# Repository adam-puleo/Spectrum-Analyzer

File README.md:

# Spectrum-Analyzer
Uses the MSGEQ7 chips and a NeoPixel matrix to display frequency volumes using a Particle Photon.

This project uses two MSGEQ7 chips (COM-10468 on SparkFun.com) to analyze sound frequencies. One chip for the left, and the other chip for the right channel. Input is via a 3.5mm audio jack. The frequency volumes, and average volume is displayed with a NeoPixel matrix (COM-13304 on SparkFun.com). Data is processed using Particle's Photon (particle.io).

The Photon uses 3.3 volts on its analog and digital pins. The MSGEQ7 and NeoPixels are 5 volts. A SN74HCT125N is used to drive the inputs on the MSGEQ7 and NeoPixel from the Photon. To read the MSGEQ7s output a voltage divider circuit is used. The MSGEQ7 seems to output 4.8 volts when a frequency is at maximum volume thus a 1.5k ohm resistor is used. Pin eight of the SN74HCT125N is used to drive the NeoPixel matrix. Gate B, output pin 6, of the SN74HCT125N is not used.

The msgeq7, spectrum_display, and neopixelmatrix libraries have been published to Particle's public libraries. Thus when you compile the code Particle will automatically link with the libraries. The 'Eagle/Audio Lights' directory contains the schematic in Autodesk's EAGLE program.

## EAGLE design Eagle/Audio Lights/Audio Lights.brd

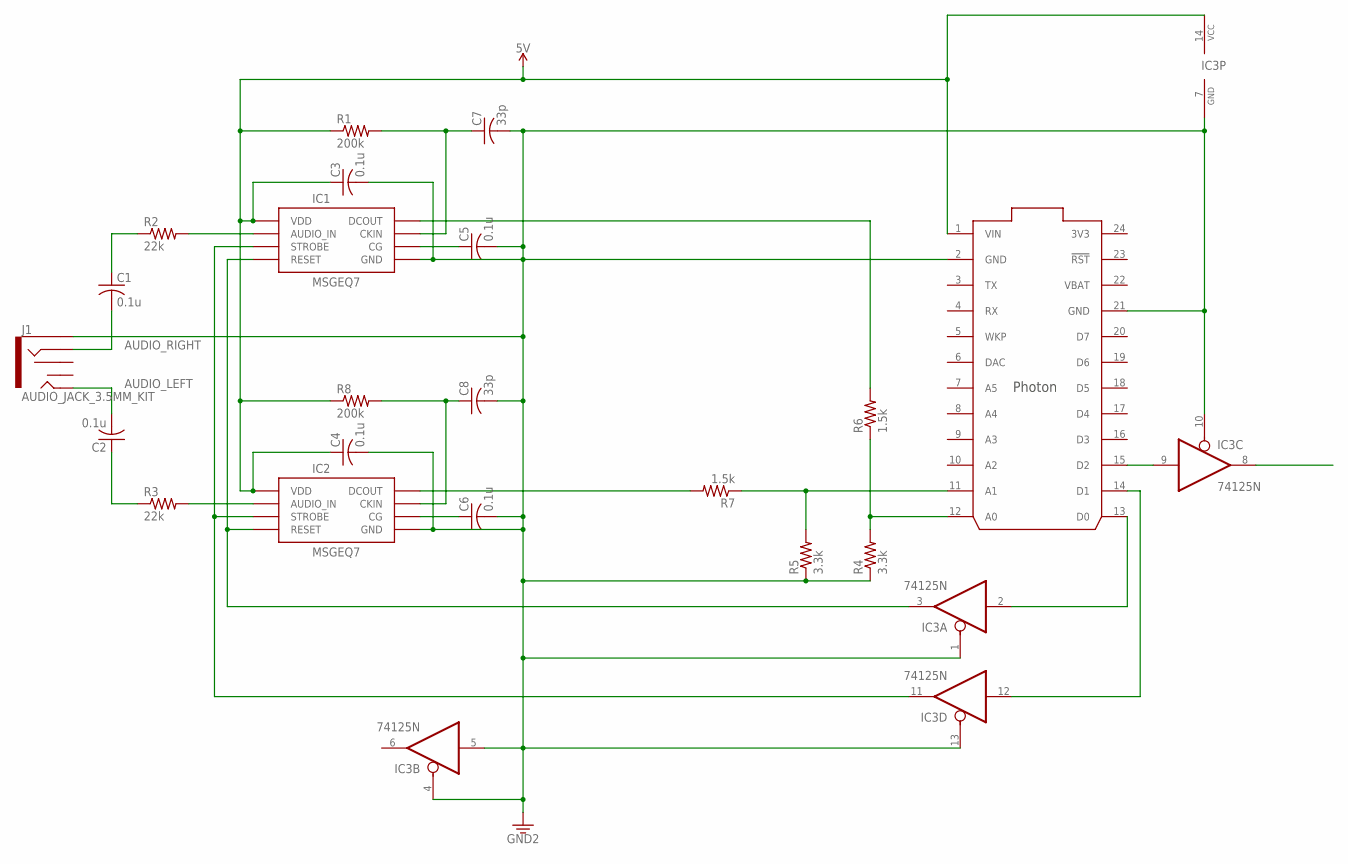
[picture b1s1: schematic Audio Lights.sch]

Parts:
C1, C2, C3, C4, C5, C6: 0.1u; C025-024X044
C7, C8: 33p; C050-045X075
IC1, IC2: MSGEQ7P; DIP08
IC3: 74125N; DIL14
J1: AUDIO_JACK_3.5MM_KIT; AUDIO-JACK-KIT
R1, R8: 200k; 0204/7
R2, R3: 22k; 0204/7
R4, R5: 3.3k; 0204/5
R6, R7: 1.5k; 0204/5
U$1: PHOTON_WITH_HEADERS; PHOTON

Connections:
3V3: U$1.24 (3V3)
5V: C3.1, C4.1, IC1.1 (VDD), IC2.1 (VDD), IC3.14 (VCC), R1.1, R8.1, U$1.1 (VIN)
AGND_LEFT: C6.1, IC2.6 (CG)
AGND_RIGHT: C5.1, IC1.6 (CG)
AUDIO_IN_LEFT: IC2.5 (AUDIO_IN), R3.2
AUDIO_IN_RIGHT: IC1.5 (AUDIO_IN), R2.2
AUDIO_LEFT: C2.2, J1.TIP
AUDIO_RIGHT: C1.2, J1.RING
CLK_LEFT: C8.1, IC2.8 (CKIN), R8.2
CLK_RIGHT: C7.1, IC1.8 (CKIN), R1.2
DOUT_LEFT3V3: R5.2, R7.1, U$1.11 (A1)
DOUT_LEFT5V: IC2.3 (DCOUT), R7.2
DOUT_RIGHT3V3: R4.2, R6.1, U$1.12 (A0)
DOUT_RIGHT5V: IC1.3 (DCOUT), R6.2
GND: C3.2, C4.2, C5.2, C6.2, C7.2, C8.2, IC1.2 (GND), IC2.2 (GND), IC3.1 (OE), IC3.4 (OE), IC3.5 (I), IC3.7 (GND), IC3.10 (OE), IC3.13 (OE), J1.SLEEVE, R4.1, R5.1, U$1.2 (GND), U$1.21 (GND)
LED_3.3V: IC3.9 (I), U$1.15 (D2)
LED_5V: IC3.8 (O)
unnamed: C2.1, R3.1
unnamed: C1.1, R2.1
RESET_3.3V: IC3.2 (I), U$1.13 (D0)
RESET_5V: IC1.7 (RESET), IC2.7 (RESET), IC3.3 (O)
STROBE_3.3V: IC3.12 (I), U$1.14 (D1)
STROBE_5V: IC1.4 (STROBE), IC2.4 (STROBE), IC3.11 (O)
VBAT: U$1.22 (VBAT)

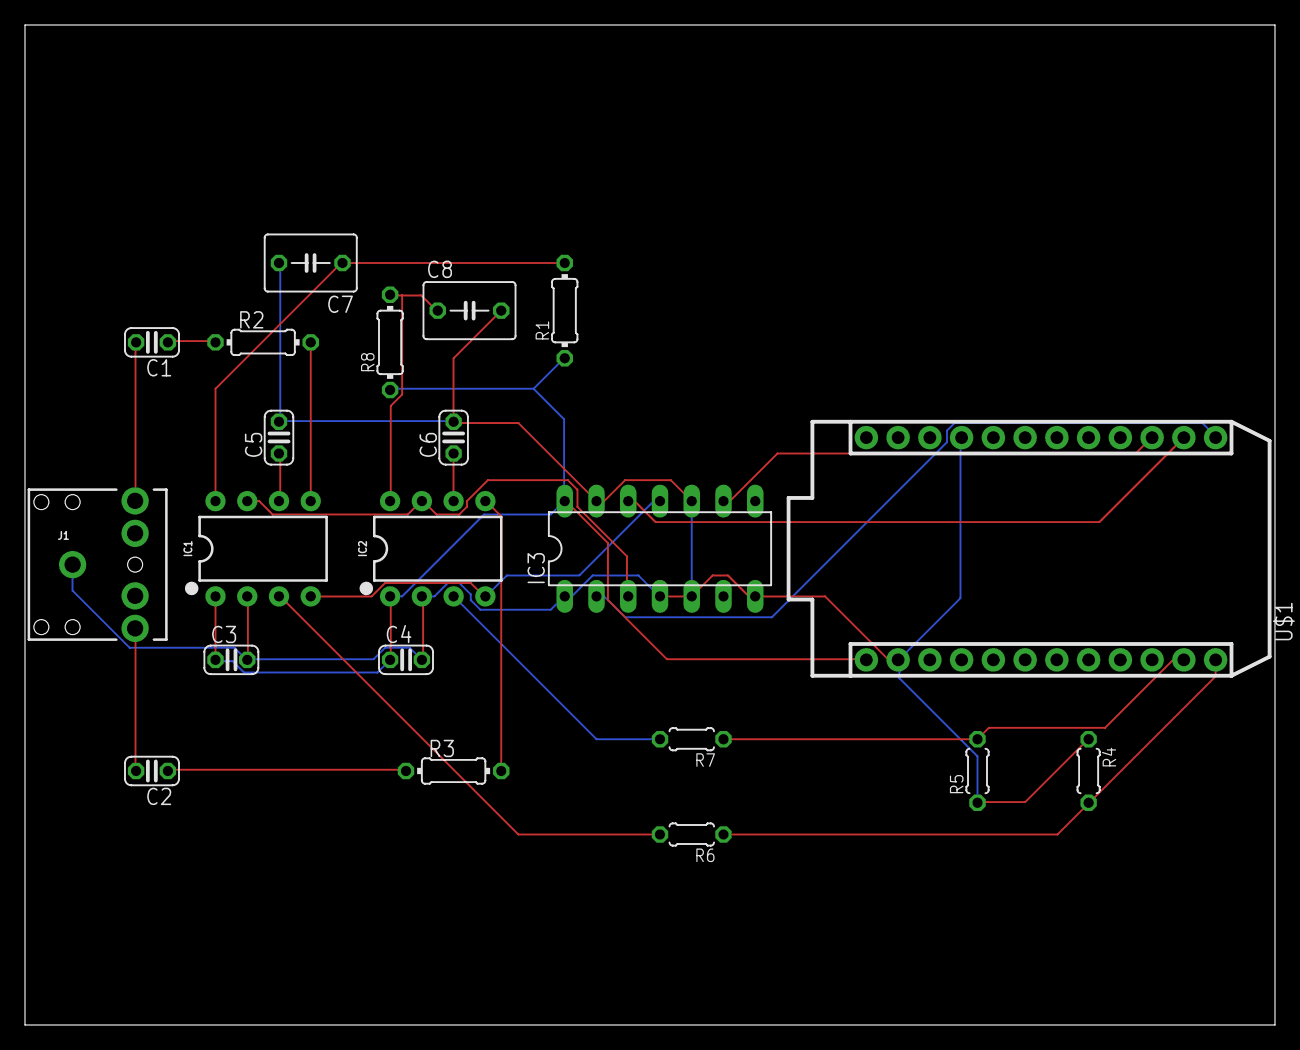
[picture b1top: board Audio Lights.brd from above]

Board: 2 copper layers, 100.0 x 80.0 mm, 21 parts (0 on the bottom side), 21 nets.

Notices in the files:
parts and their libraries:
SparkFun-IC-Special-Function: Licensing: Creative Commons ShareAlike 4.0 International - https://creativecommons.org/licenses/by-sa/4.0
Particle-Devices: Licensing: Designed by Particle.
